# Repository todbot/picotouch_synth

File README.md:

# picotouch_synth

Thin captouch-based synth platform for Raspberry Pi Pico

Features:
* Raspberry Pi Pico
* PWM Audio out
* TRS-A MIDI In / Out
* USB MIDI In/Out
* 19 RGB LEDs
* 22 touch pads (17 notes, 5 modifiers)
* Low part count: [14 BOM line items, mostly passives](./schematics/picotouch_synth_flip_bottom_bom.csv)
* Completely flat surface (only reverse-mount LEDs, capsense pads)
* 6 mm thick when in [minimal enclosure](https://github.com/todbot/picotouch_synth/tree/main/enclosure)
   (255 x 42 x 6 mm volume)

## Installing firmware

There are currently three "applications" for the picotouch_synth board, all are in active development,
so check the [Release page](https://github.com/todbot/picotouch_synth/releases)
for latest versions as prebuilt UF2 images.

- [picotouch_synth](./circuitpython/picotouch_synth) -- a wavetable synth with three different patches
  ([video demo](https://www.youtube.com/watch?v=0FgqWdkIjWM))
- [pts_drum_machine](./circuitpython/pts_drum_machine) -- a drum sample player
  ([video demo](https://www.youtube.com/watch?v=OaN6xVYXhNE))
- [hwtest](./circuitpython/hwtest/) -- simple hardware test of the board

### Installing prebuilt UF2 images

Instead of installing CircuitPython, then installling needed libraries,
and finally installing the code you want, you can just copy a UF2 file to the RPI-RP2 bootloader drive!

As a rule, all firmware will be offered as pre-built firmware UF2 images for picotouch_synth.
Go to the [Releases](https://github.com/todbot/picotouch_synth/releases) page
and download the UF2 you want.  Then, to install:

* Unplug picotouch_synth PCB board from USB
* Unclip PCB from case ([see this video on releasing the case](https://youtu.be/MjScFP873SQ))
* Hold BOOT button on Pico while plugging back into USB
* Copy the UF2 file to the RPI-RP2 drive
* When board finishes reflashing, it will reboot

__Note:__ if your Pico has more than the 2 MB standard flash
(like the [purple "RetroScaler" 16MB USB-C ones](https://www.aliexpress.us/item/3256804731684211.html)),
the UF2s will still work but the resulting CIRCUITPY drive only be 1 MB.
To get the flash space back, you will need to
[install CircuitPython](https://learn.adafruit.com/welcome-to-circuitpython/installing-circuitpython#for-rp2040-boards-3105171)
and install the code files by hand.

## Sketching in Hardware 2023 Edition

For the Sketching in Hardware conference, the firmware shipped on the boards is in
[circuitpython/picotouch_synth](https://github.com/todbot/picotouch_synth/tree/main/circuitpython/picotouch_synth)
and the pre-built UF2 firwmare in the [Releases section](https://github.com/todbot/picotouch_synth/releases/tag/v1).

There were two different boards handed out:
- [micro-USB green Raspberry Pi Picos w/ 2 MB flash](https://www.raspberrypi.com/documentation/microcontrollers/raspberry-pi-pico.html)
- [USB-C purple "RetroScaler" Pico clones w/ 16 MB flash](https://www.aliexpress.us/item/3256804731684211.html).

Both are formated as 2MB devices so if you have a purple board and want the extra flash space,
you'll need to
[install CircuitPython](https://learn.adafruit.com/welcome-to-circuitpython/installing-circuitpython#for-rp2040-boards-3105171)
and the code files by hand.

### The picotouch_synth application

The keyboard is laid out as top row is modulators (three groups of "sliders")
and the bottom row plays notes in a particular scale.
The A/B/C buttons select different sounds and the X/Y buttons on the right transpose up/down octaves.

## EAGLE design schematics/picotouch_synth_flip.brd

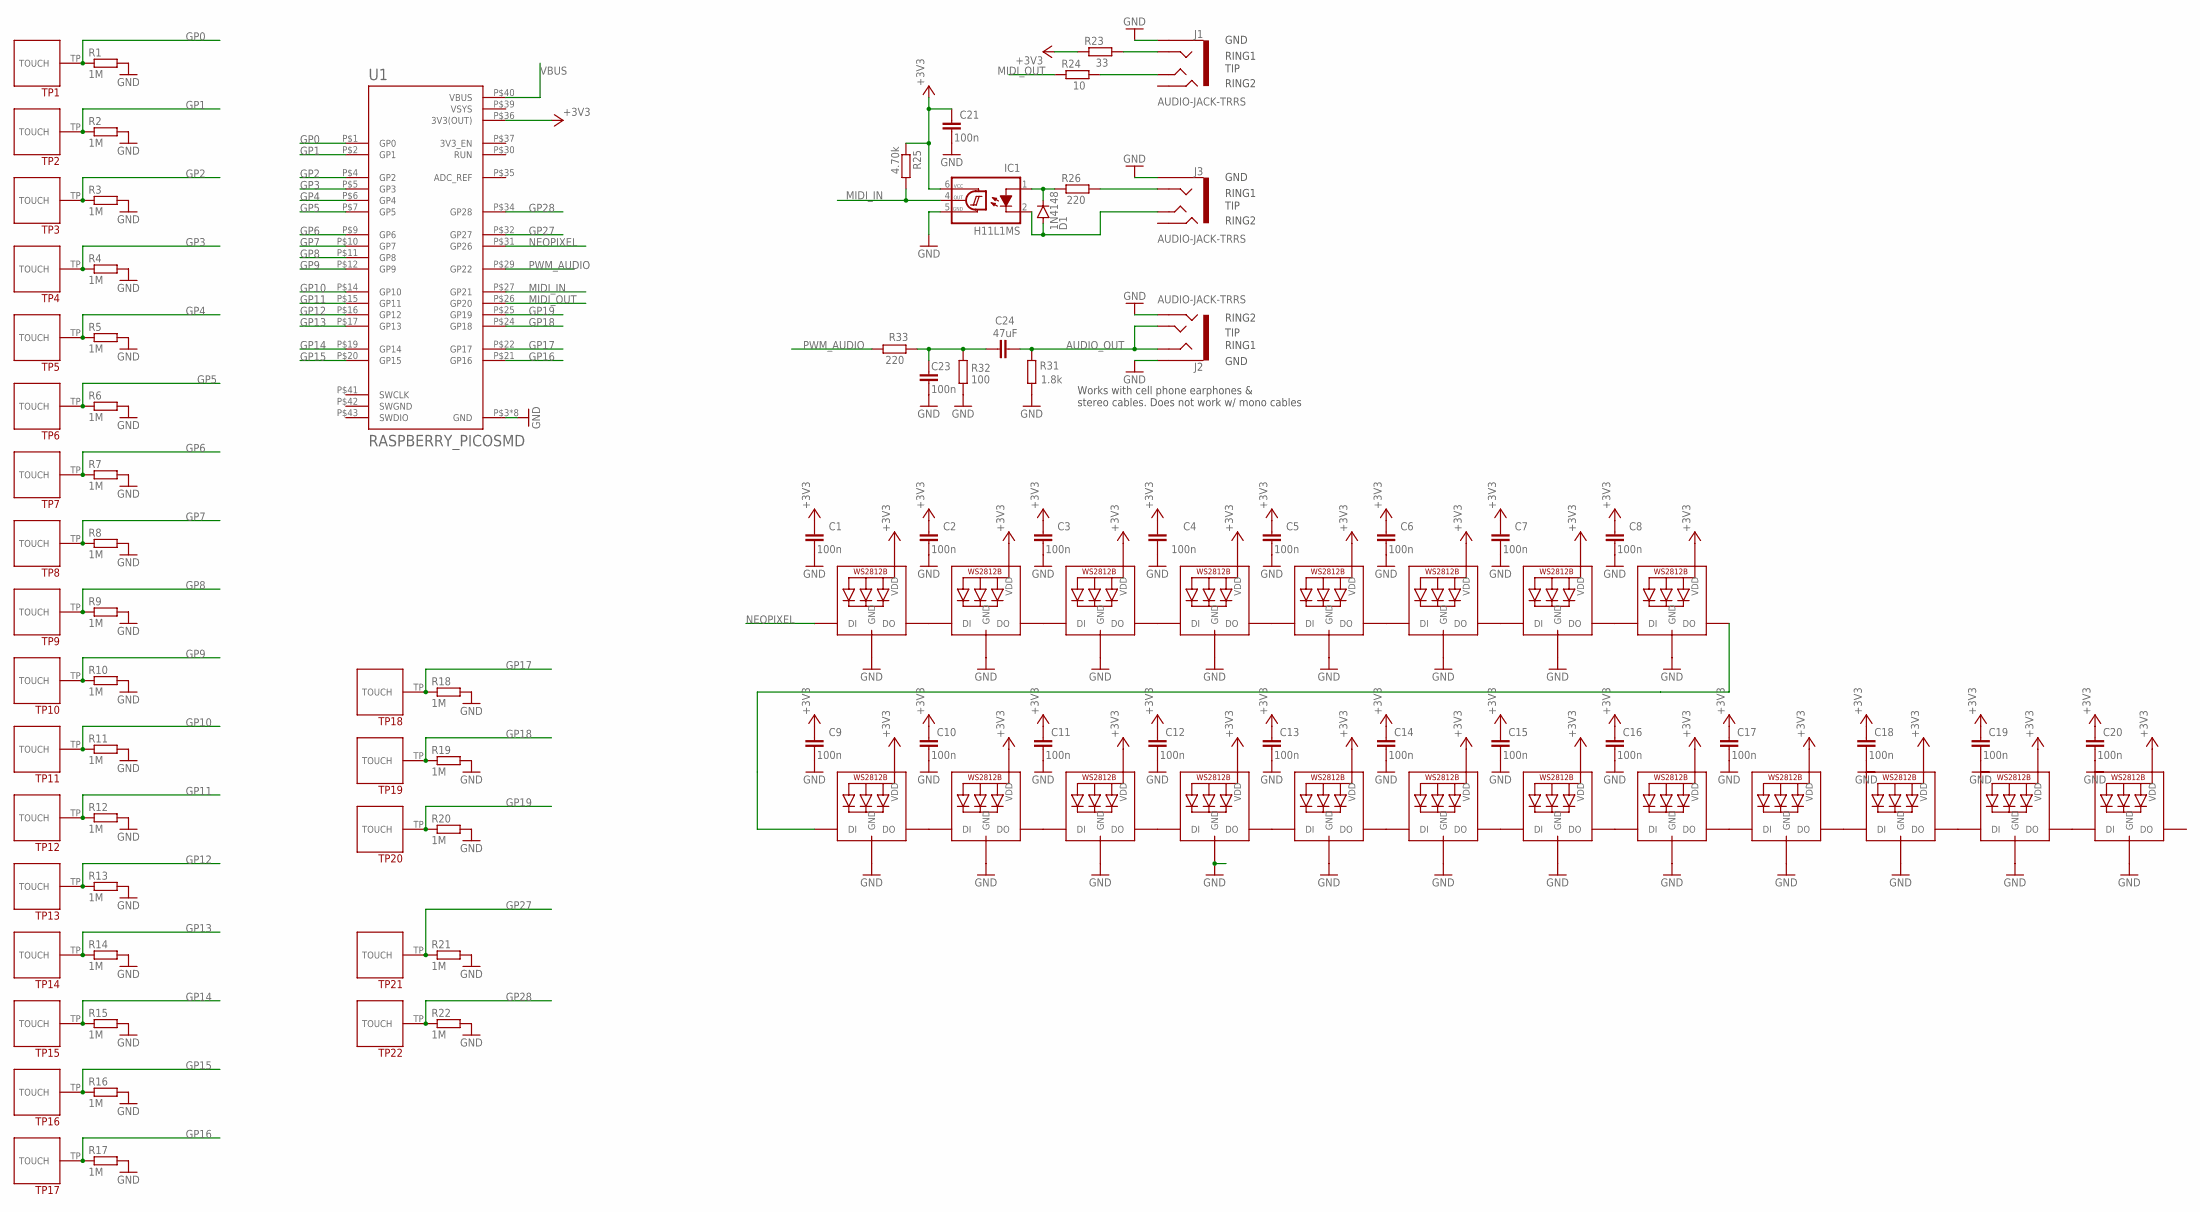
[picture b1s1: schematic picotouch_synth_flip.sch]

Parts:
C1, C2, C3, C4, C5, C6, C7, C8, C9, C10, C11, C12, C13, C14, C15, C16, C17, C18, C19, C20, C21, C23: 100n; C0603
C24: 47uF; C0603
D1: 1N4148; SOD123
IC1: H11L1MS; DIL6-SMD; MPN2 H11L1S; LCSC C78589
J1, J3: AUDIO-JACK-TRRS; PJ-320D_SPARKFUN
J2: AUDIO-JACK-TRRS; PJ-320D_SPARKFUN; LCSC C431535
LED1, LED2, LED3, LED4, LED5, LED6, LED7, LED8, LED9, LED10, LED11, LED12, LED13, LED14, LED15, LED16, LED17, LED18, LED19, LED20: MICROBUILDER_WS2812B_SK6812E; MICROBUILDER_NEO3535_REVERSE
R1, R2, R3, R4, R5, R6, R7, R8, R9, R10, R11, R12, R13, R14, R15, R16, R17: 1M; R0805
R18, R19, R20, R21, R22: 1M; R0603
R23: 33; R0603
R24: 10; R0603
R25: 4.70k; R0603
R26, R33: 220; R0603
R31: 1.8k; R0603
R32: 100; R0603
TP1, TP2, TP3, TP4, TP5, TP6, TP7, TP8, TP9, TP10, TP11, TP12, TP13, TP14, TP15, TP16, TP17: TOUCHPADA
TP18, TP19, TP20, TP21, TP22: TOUCHPADB
U1: RASPBERRY_PICOSMD; PICO-PKG-SMD

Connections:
+3V3: C1.1, C2.1, C3.1, C4.1, C5.1, C6.1, C7.1, C8.1, C9.1, C10.1, C11.1, C12.1, C13.1, C14.1, C15.1, C16.1, C17.1, C18.1, C19.1, C20.1, C21.1, IC1.6 (VCC), LED1.1-VDD (VDD), LED2.1-VDD (VDD), LED3.1-VDD (VDD), LED4.1-VDD (VDD), LED5.1-VDD (VDD), LED6.1-VDD (VDD), LED7.1-VDD (VDD), LED8.1-VDD (VDD), LED9.1-VDD (VDD), LED10.1-VDD (VDD), LED11.1-VDD (VDD), LED12.1-VDD (VDD), LED13.1-VDD (VDD), LED14.1-VDD (VDD), LED15.1-VDD (VDD), LED16.1-VDD (VDD), LED17.1-VDD (VDD), LED18.1-VDD (VDD), LED19.1-VDD (VDD), LED20.1-VDD (VDD), R23.1, R25.1, U1.P$36 (3V3(OUT))
AUDIO_OUT: C24.2, J2.RING1, J2.TIP, R31.1
GND: C1.2, C2.2, C3.2, C4.2, C5.2, C6.2, C7.2, C8.2, C9.2, C10.2, C11.2, C12.2, C13.2, C14.2, C15.2, C16.2, C17.2, C18.2, C19.2, C20.2, C21.2, C23.2, IC1.5 (GND), J1.EARTH, J2.EARTH, J2.RING2, J3.EARTH, LED1.3-GND (GND), LED2.3-GND (GND), LED3.3-GND (GND), LED4.3-GND (GND), LED5.3-GND (GND), LED6.3-GND (GND), LED7.3-GND (GND), LED8.3-GND (GND), LED9.3-GND (GND), LED10.3-GND (GND), LED11.3-GND (GND), LED12.3-GND (GND), LED13.3-GND (GND), LED14.3-GND (GND), LED15.3-GND (GND), LED16.3-GND (GND), LED17.3-GND (GND), LED18.3-GND (GND), LED19.3-GND (GND), LED20.3-GND (GND), R1.2, R2.2, R3.2, R4.2, R5.2, R6.2, R7.2, R8.2, R9.2, R10.2, R11.2, R12.2, R13.2, R14.2, R15.2, R16.2, R17.2, R18.2, R19.2, R20.2, R21.2, R22.2, R31.2, R32.1, U1.P$3 (GND), U1.P$8 (GND), U1.P$13 (GND), U1.P$18 (GND), U1.P$23 (GND), U1.P$28 (GND), U1.P$33 (GND), U1.P$38 (GND)
GP0: R1.1, TP1.TP, U1.P$1 (GP0)
GP1: R2.1, TP2.TP, U1.P$2 (GP1)
GP2: R3.1, TP3.TP, U1.P$4 (GP2)
GP3: R4.1, TP4.TP, U1.P$5 (GP3)
GP4: R5.1, TP5.TP, U1.P$6 (GP4)
GP5: R6.1, TP6.TP, U1.P$7 (GP5)
GP6: R7.1, TP7.TP, U1.P$9 (GP6)
GP7: R8.1, TP8.TP, U1.P$10 (GP7)
GP8: R9.1, TP9.TP, U1.P$11 (GP8)
GP9: R10.1, TP10.TP, U1.P$12 (GP9)
GP10: R11.1, TP11.TP, U1.P$14 (GP10)
GP11: R12.1, TP12.TP, U1.P$15 (GP11)
GP12: R13.1, TP13.TP, U1.P$16 (GP12)
GP13: R14.1, TP14.TP, U1.P$17 (GP13)
GP14: R15.1, TP15.TP, U1.P$19 (GP14)
GP15: R16.1, TP16.TP, U1.P$20 (GP15)
GP16: R17.1, TP17.TP, U1.P$21 (GP16)
GP17: R18.1, TP18.TP, U1.P$22 (GP17)
GP18: R19.1, TP19.TP, U1.P$24 (GP18)
GP19: R20.1, TP20.TP, U1.P$25 (GP19)
GP27: R21.1, TP21.TP, U1.P$32 (GP27)
GP28: R22.1, TP22.TP, U1.P$34 (GP28)
MIDI_IN: IC1.4 (OUT), R25.2, U1.P$27 (GP21)
MIDI_OUT: R24.1, U1.P$26 (GP20)
unnamed: D1.C, IC1.1 (A), R26.1
unnamed: J1.TIP, R24.2
unnamed: D1.A, IC1.2 (C), J3.TIP
unnamed: J3.RING1, R26.2
unnamed: C23.1, C24.1, R32.2, R33.1
unnamed: J1.RING1, R23.2
unnamed: LED1.2-DOUT (DO), LED2.4-DIN (DI)
unnamed: LED2.2-DOUT (DO), LED3.4-DIN (DI)
unnamed: LED4.2-DOUT (DO), LED5.4-DIN (DI)
unnamed: LED5.2-DOUT (DO), LED6.4-DIN (DI)
unnamed: LED6.2-DOUT (DO), LED7.4-DIN (DI)
unnamed: LED7.2-DOUT (DO), LED8.4-DIN (DI)
unnamed: LED9.2-DOUT (DO), LED10.4-DIN (DI)
unnamed: LED10.2-DOUT (DO), LED11.4-DIN (DI)
unnamed: LED12.2-DOUT (DO), LED13.4-DIN (DI)
unnamed: LED13.2-DOUT (DO), LED14.4-DIN (DI)
unnamed: LED14.2-DOUT (DO), LED15.4-DIN (DI)
unnamed: LED15.2-DOUT (DO), LED16.4-DIN (DI)
unnamed: LED3.2-DOUT (DO), LED4.4-DIN (DI)
unnamed: LED11.2-DOUT (DO), LED12.4-DIN (DI)
unnamed: LED8.2-DOUT (DO), LED9.4-DIN (DI)
unnamed: LED16.2-DOUT (DO), LED17.4-DIN (DI)
unnamed: LED17.2-DOUT (DO), LED18.4-DIN (DI)
unnamed: LED18.2-DOUT (DO), LED19.4-DIN (DI)
unnamed: LED19.2-DOUT (DO), LED20.4-DIN (DI)
NEOPIXEL: LED1.4-DIN (DI), U1.P$31 (GP26)
PWM_AUDIO: R33.2, U1.P$29 (GP22)
SWGND: U1.P$42 (SWGND)
VBUS: U1.P$40 (VBUS)
VSYS: U1.P$39 (VSYS)

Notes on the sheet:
RING2
RING1
GND
TIP
Works with cell phone earphones & stereo cables. Does not work w/ mono cables

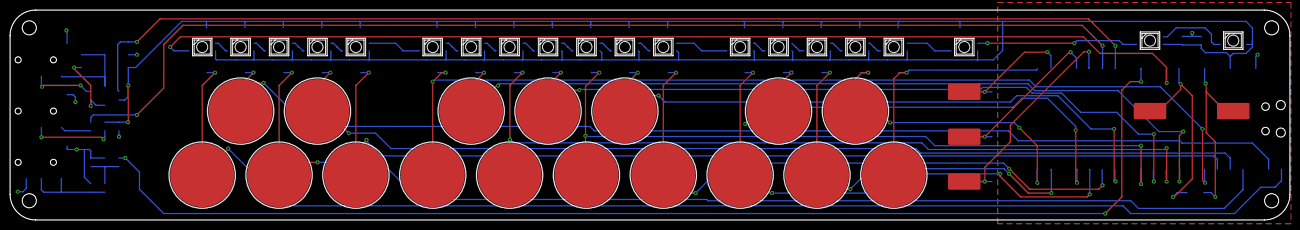
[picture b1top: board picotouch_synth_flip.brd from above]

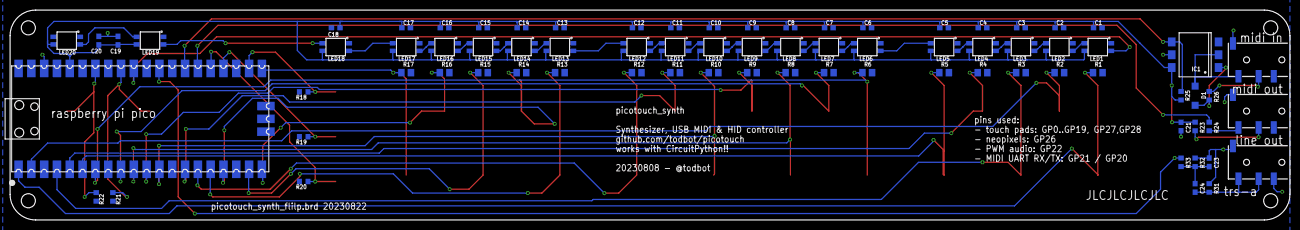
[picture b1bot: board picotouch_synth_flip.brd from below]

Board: 2 copper layers, 253.7 x 41.5 mm, 100 parts (58 on the bottom side), 54 nets.

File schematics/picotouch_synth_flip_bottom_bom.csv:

Comment,Designator,Footprint,LCSC Part #
1.8k,R31,R0603,
1M,R1 R2 R3 R4 R5 R6 R7 R8 R9 R10 R11 R12 R13 R14 R15 R16 R17,R0805,
1M,R18 R19 R20 R21 R22,R0603,
1N4148,D1,SOD123,
4.70k,R25,R0603,
10,R24,R0603,
33,R23,R0603,
47uF,C24,C0603,
100,R32,R0603,
100n,C1 C2 C3 C4 C5 C6 C7 C8 C9 C10 C11 C12 C13 C14 C15 C16 C17 C18 C19 C20 C21 C23,C0603,
220,R26 R33,R0603,
AUDIO-JACK-TRRS,J1 J2 J3,PJ-320D_SPARKFUN,C431535
H11L1MS,IC1,DIL6-SMD,C78589
MICROBUILDER_WS2812B_SK6812E,LED1 LED2 LED3 LED4 LED5 LED6 LED7 LED8 LED9 LED10 LED11 LED12 LED13 LED14 LED15 LED16 LED17 LED18 LED19 LED20,MICROBUILDER_NEO3535_REVERSE,
RASPBERRY_PICOSMD,U1,PICO-PKG-SMD,

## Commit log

2022-12-01 picotouchsynth now has its own repo
2022-12-01 simple touch test works
2022-12-01 added cadshots
2022-12-01 add led test to hw test
2022-12-03 mozzi started
2022-12-04 now captouch buttons work as keyboard
2022-12-04 now with LEDs
2022-12-04 now with fading LEDs
2022-12-04 touch bugfixes
2022-12-04 display now
2022-12-04 monosynth1 cleanup
2022-12-04 add circles
2023-08-16 moved from picotouch repo
2023-08-16 arranging deck chairs
2023-08-16 commit before fab
2023-08-16 some git sanity until I figure out what to do with old ideas
2023-08-17 update README with PCB renders
2023-08-17 moved topsilk to tNames so it renders
2023-08-22 sync up
2023-08-22 forgot to wire 3v3. wow I am really dumb
2023-08-23 flip version
2023-08-23 flip version updates
2023-08-30 fix silkscreen jack labels
2023-08-30 last artwork update before submit to fab
2023-09-13 sync
2023-09-18 update docs
2023-09-20 add sketching2023 guide image
2023-09-21 case checkin, "v29" in fusion
2023-09-21 update sketching diag
2023-09-21 pdf of sch
2023-09-21 add afdesign of sketching firmware ui
2023-09-22 doc update
2023-09-22 docs
2023-09-23 add bom and cpl
2023-09-23 typo
2023-10-08 add midi in/out, add better scales, fix octave pad bug
2023-10-08 first cut at drum machine
2023-10-08 fix patch setup for patchC, and use PLAITS03 instead
2023-10-08 pts_drum_machine fixes, still just a sample player
2023-10-08 make pic bigger
2023-10-08 update docs about different sketching board types
2023-10-08 more sketching docs
2023-10-08 small video on how to release the PCB from the case
2023-10-09 patch tuning
2023-10-09 ignore uf2 in git
2023-10-10 cleanup sch directory
2023-10-10 cleanup docs dir
2023-10-11 change to DIY debouncing: full keyscan goes from 25 millis to 9 milllis
2023-10-15 new picotouch_synth.py with much faster touch reading (do not need adafruit_debouncer)
2023-10-15 add debug timing to check_touch
2023-10-15 let's try symlinks for these libraries
2024-12-05 add new easier to use case
